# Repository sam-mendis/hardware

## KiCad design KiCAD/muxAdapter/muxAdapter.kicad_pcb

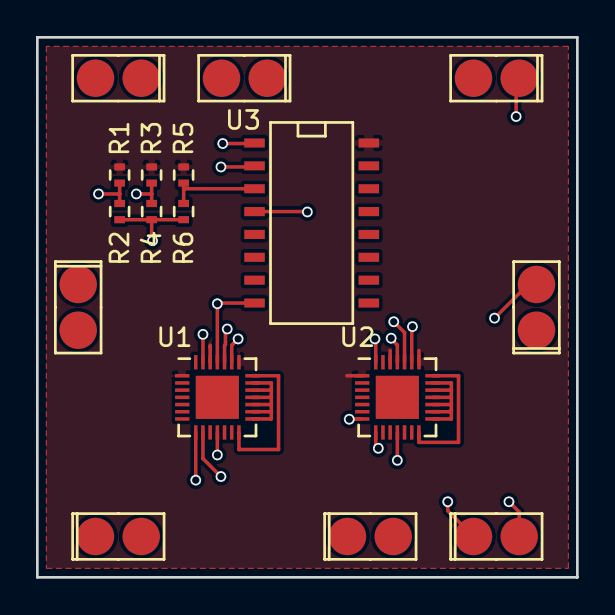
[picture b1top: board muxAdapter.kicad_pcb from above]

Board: 4 copper layers, 30.0 x 30.0 mm, 55 parts (38 on the bottom side), 29 nets.

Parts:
P1, P2, P3, P4, P5, P6, P7, P8, P9, P10, P11, P12, P13, P14, P15, P16, P17, P18, P19, P20, P21, P22, P23, P24, P25, P26, P27, P28, P29, P30, P31, P32, P33, P34, P35, P36, P37, P38: CONN_01X01; 0508-0-00-15-00-00-03-0
P39, P40, P41, P42, P43, P44, P45, P46: CONN_01X02; 812-22-002-30-007101
R1, R2, R3, R4, R5, R6: R; R_0402
U1, U2: MAX14662; QFN-28-1EP_4x4mm_Pitch0.4mm
U3: PCF8574; SO-16-N

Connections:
0_I: P40.2, U1.3
0_V: P40.1, U2.3
1_I: P41.1, U1.4
1_V: P41.2, U2.4
2_I: P42.2, U1.5
2_V: P42.1, U2.5
3_I: P43.1, U1.6
3_V: P43.2, U2.6
4_I: P44.2, U1.7
4_V: P44.1, U2.7
5_I: P45.1, U1.8
5_V: P45.2, U2.8
+5V: R1.1, R3.1, R5.1, U1.1, U1.22, U1.26, U2.1, U2.22, U2.26, U3.16
A0: R1.2, R2.1, U3.1
A1: R3.2, R4.1, U3.2
A2: R5.2, R6.1, U3.3
GND: R2.2, R4.2, R6.2, U1.11, U1.25, U2.11, U2.25, U3.8
I+: U1.15, U1.16, U1.17, U1.18, U1.19, U1.20
I-: U1.14, U1.21
L_I: P39.1, U1.2
L_V: P39.2, U2.2
MOSI: U1.27, U2.27
unnamed: U1.23, U2.28
R_I: P46.2, U1.9
R_V: P46.1, U2.9
SCK: U1.24, U2.24
SM_CS: U2.23, U3.4
V+: U2.15, U2.16, U2.17, U2.18, U2.19, U2.20
V-: U2.14, U2.21

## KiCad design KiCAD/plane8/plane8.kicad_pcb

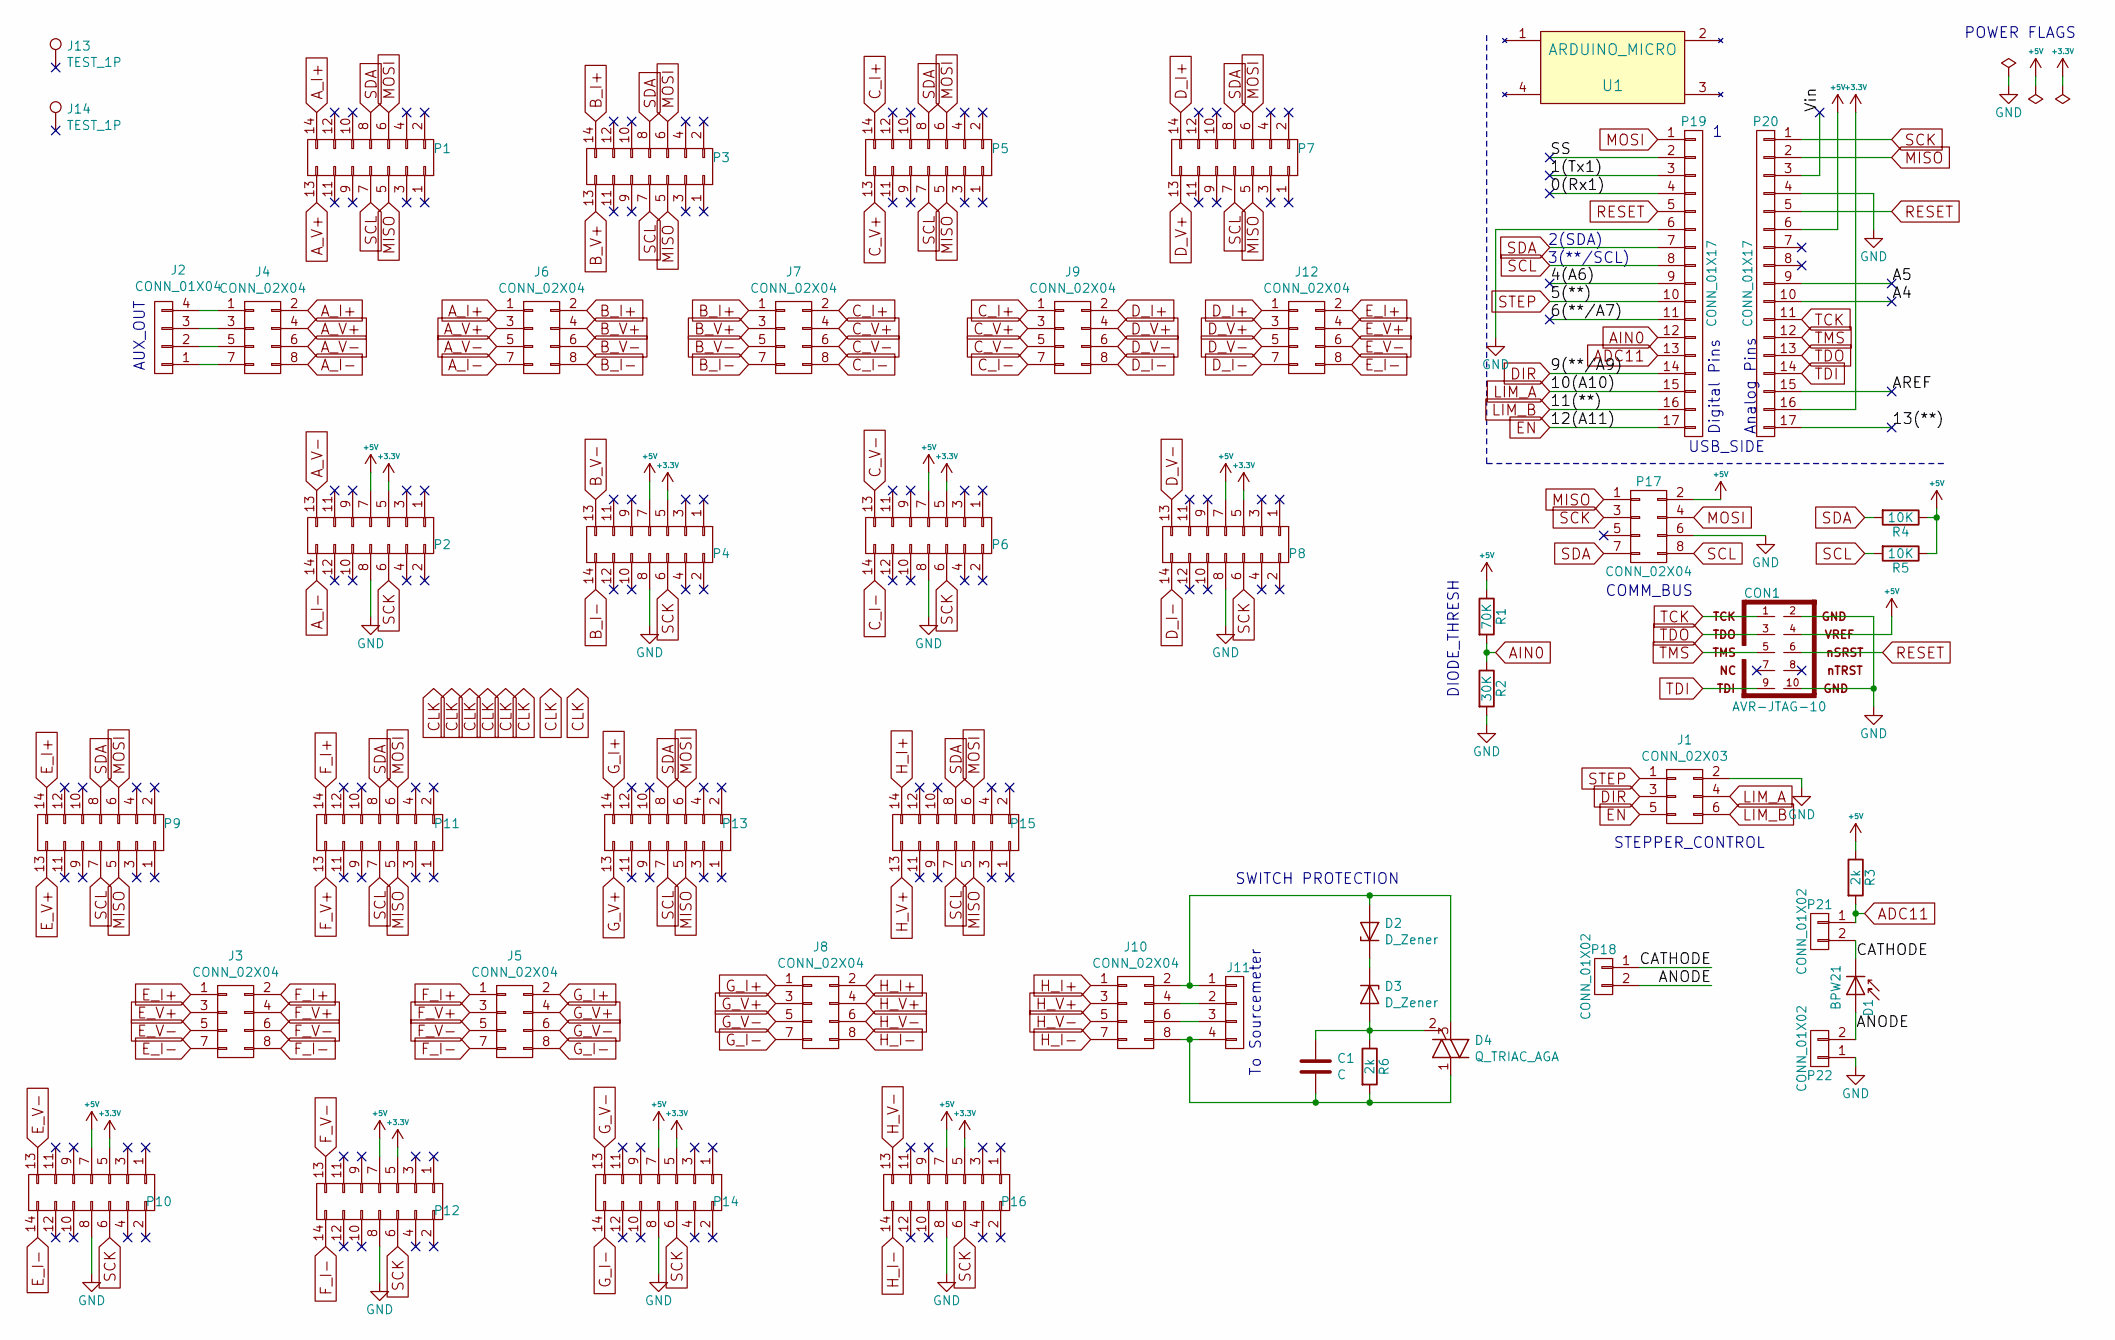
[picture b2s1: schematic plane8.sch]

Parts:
C1: C; C_0805_HandSoldering
CON1: AVR-JTAG-10; Pin_Header_Straight_2x05_Pitch2.54mm
D1: BPW21
D2, D3: D_Zener; D_DO-41_SOD81_P10.16mm_Horizontal
D4: Q_TRIAC_AGA; TO-92_Horizontal1_Molded_Narrow
J1: CONN_02X03; Pin_Header_Straight_2x03_Pitch2.54mm
J2, J11: CONN_01X04; Pin_Header_Angled_1x04_Pitch2.54mm
J3, J4, J5, J6, J7, J8, J9, J10, J12: CONN_02X04; Pin_Header_Straight_2x04_Pitch2.54mm
J13, J14: TEST_1P; MountingHole_2.2mm_M2_Pad
P1, P3, P5, P7, P9, P11, P13, P15: CONN_02X07; TSW-107-22-T-D-INV
P2, P4, P6, P8, P10, P12, P14, P16: CONN_02X07; TSW-107-22-T-D
P17: CONN_02X04; Pin_Header_Straight_2x04_Pitch2.54mm
P18, P21, P22: CONN_01X02; Pin_Header_Straight_1x02_Pitch2.54mm
P19, P20: CONN_01X17; Socket_Strip_Straight_1x17_Pitch2.54mm
R1: 70K; R_0805_HandSoldering
R2: 30K; R_0805_HandSoldering
R3, R6: 2k; R_0805_HandSoldering
R4, R5: 10K; R_0805_HandSoldering
U1: ARDUINO_MICRO; arduino_micro

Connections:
+3V3: P2.5, P4.5, P6.5, P8.5, P10.5, P12.5, P14.5, P16.5, P20.16
+5V: CON1.4, P2.7, P4.7, P6.7, P8.7, P10.7, P12.7, P14.7, P16.7, P17.2, P20.6, R1.1, R3.1, R4.1, R5.1
/0(Rx1): P19.4
/1(Tx1): P19.3
/4(A6): P19.9
/6(**/A7): P19.11
/13(**): P20.17
/A4: P20.10
/A5: P20.9
/ANODE: D1.2 (A), P18.2, P22.2
/AREF: P20.15
/CATHODE: D1.1 (K), P18.1, P21.2
/SS: P19.2
/Vin: P20.3
ADC11: P19.13, P21.1, R3.2
AIN0: P19.12, R1.2, R2.1
A_I+: J4.2, J6.1, P1.14
A_I-: J4.8, J6.7, P2.14
A_V+: J4.4, J6.3, P1.13
A_V-: J4.6, J6.5, P2.13
B_I+: J6.2, J7.1, P3.14
B_I-: J6.8, J7.7, P4.14
B_V+: J6.4, J7.3, P3.13
B_V-: J6.6, J7.5, P4.13
C_I+: J7.2, J9.1, P5.14
C_I-: J7.8, J9.7, P6.14
C_V+: J7.4, J9.3, P5.13
C_V-: J7.6, J9.5, P6.13
DIR: J1.3, P19.14
D_I+: J9.2, J12.1, P7.14
D_I-: J9.8, J12.7, P8.14
D_V+: J9.4, J12.3, P7.13
D_V-: J9.6, J12.5, P8.13
EN: J1.5, P19.17
E_I+: J3.1, J12.2, P9.14
E_I-: J3.7, J12.8, P10.14
E_V+: J3.3, J12.4, P9.13
E_V-: J3.5, J12.6, P10.13
F_I+: J3.2, J5.1, P11.14
F_I-: J3.8, J5.7, P12.14
F_V+: J3.4, J5.3, P11.13
F_V-: J3.6, J5.5, P12.13
GND: CON1.2, CON1.10, J1.2, P2.8, P4.8, P6.8, P8.8, P10.8, P12.8, P14.8, P16.8, P17.6, P19.6, P20.4, P22.1, R2.2
G_I+: J5.2, J8.1, P13.14
G_I-: J5.8, J8.7, P14.14
G_V+: J5.4, J8.3, P13.13
G_V-: J5.6, J8.5, P14.13
H_I+: J8.2, J10.1, P15.14
H_I-: J8.8, J10.7, P16.14
H_V+: J8.4, J10.3, P15.13
H_V-: J8.6, J10.5, P16.13
LIM_A: J1.4, P19.15
LIM_B: J1.6, P19.16
MISO: P1.5, P3.5, P5.5, P7.5, P9.5, P11.5, P13.5, P15.5, P17.1, P20.2
MOSI: P1.6, P3.6, P5.6, P7.6, P9.6, P11.6, P13.6, P15.6, P17.4, P19.1
unnamed: C1.1, D3.2 (A), D4.2 (G), R6.1
unnamed: C1.2, D4.1 (A1), J10.8, J11.4, R6.2
unnamed: D2.1 (K), D3.1 (K)
unnamed: D2.2 (A), D4.3 (A2), J10.2, J11.1
unnamed: J2.1, J4.7
unnamed: J2.2, J4.5
unnamed: J2.3, J4.3
unnamed: J2.4, J4.1
unnamed: J10.4, J11.2
unnamed: J10.6, J11.3
RESET: CON1.6, P19.5, P20.5
SCK: P2.6, P4.6, P6.6, P8.6, P10.6, P12.6, P14.6, P16.6, P17.3, P20.1
SCL: P1.7, P3.7, P5.7, P7.7, P9.7, P11.7, P13.7, P15.7, P17.8, P19.8, R5.2
SDA: P1.8, P3.8, P5.8, P7.8, P9.8, P11.8, P13.8, P15.8, P17.7, P19.7, R4.2
STEP: J1.1, P19.10
TCK: CON1.1, P20.11
TDI: CON1.9, P20.14
TDO: CON1.3, P20.13
TMS: CON1.5, P20.12

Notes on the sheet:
3(**/SCL)
2(SDA)
Digital Pins
Analog Pins
COMM_BUS
USB_SIDE
POWER FLAGS
STEPPER_CONTROL
To Sourcemeter
AUX_OUT
DIODE_THRESH
SWITCH PROTECTION

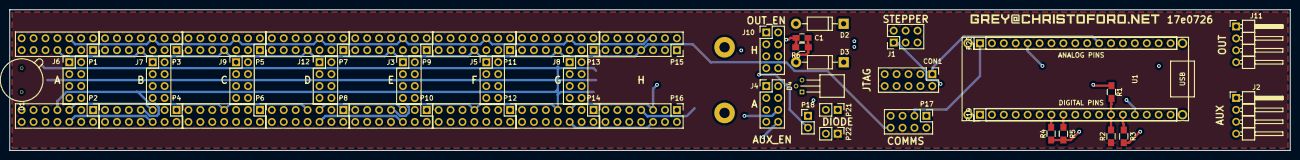
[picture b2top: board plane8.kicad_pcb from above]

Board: 4 copper layers, 273.0 x 30.0 mm, 49 parts (0 on the bottom side), 64 nets.

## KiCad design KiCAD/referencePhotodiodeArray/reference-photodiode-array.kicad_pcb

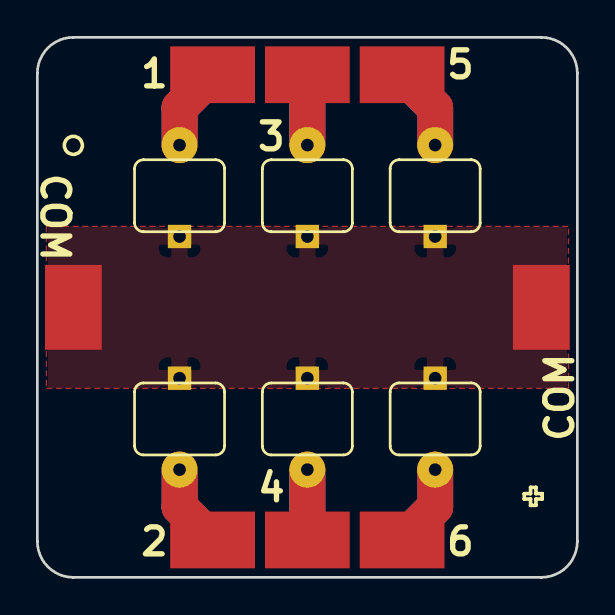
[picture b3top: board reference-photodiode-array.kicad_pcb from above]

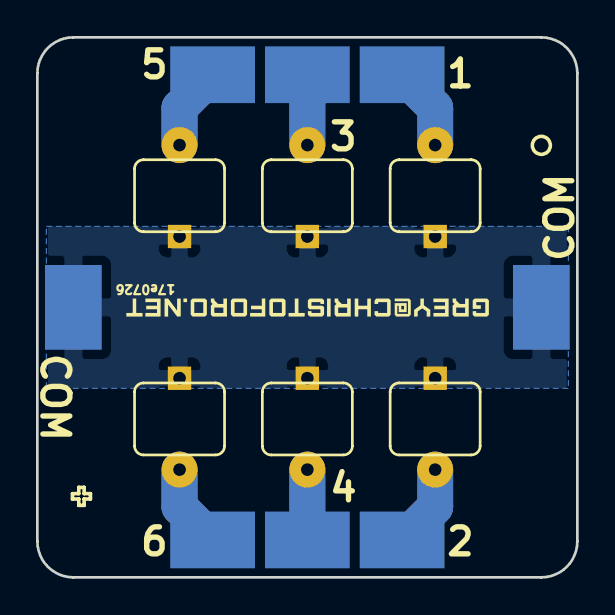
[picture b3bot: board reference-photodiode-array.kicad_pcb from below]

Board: 2 copper layers, 30.0 x 30.0 mm, 22 parts (14 on the bottom side), 7 nets.

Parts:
D1, D2, D3, D4, D5, D6: D_Photo; BPW34
W1, W2, W3, W4, W5, W6, W7, W10, W11, W12, W13, W14, W15, W16, W17, W20: TEST_1P; SolderWirePad_single_SMD_4.7x3.2mm

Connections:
/com: D1.1, D2.1, D3.1, D4.1, D5.1, D6.1, W1.1, W10.1, W11.1, W20.1
unnamed: D1.2, W2.1, W12.1
unnamed: D2.2, W3.1, W13.1
unnamed: D3.2, W4.1, W14.1
unnamed: D4.2, W5.1, W15.1
unnamed: D5.2, W6.1, W16.1
unnamed: D6.2, W7.1, W17.1

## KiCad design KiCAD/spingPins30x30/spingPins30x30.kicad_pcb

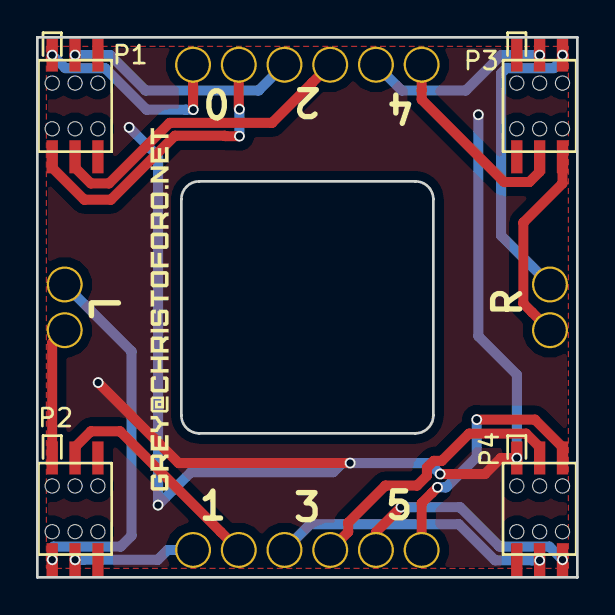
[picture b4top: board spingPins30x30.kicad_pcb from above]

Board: 2 copper layers, 30.0 x 30.0 mm, 20 parts (0 on the bottom side), 16 nets.

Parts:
P1, P2, P3, P4: CONN_02X03; RSM-103-02-L-D
TP1, TP2, TP3, TP4, TP5, TP6, TP7, TP8, TP9, TP10, TP11, TP12, TP13, TP14, TP15, TP16: TEST; S25-022+P25-4023

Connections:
0_I: P1.2, TP5.1
0_V: P1.1, TP3.1
1_I: P2.4, TP4.1
1_V: P2.3, TP6.1
2_I: P1.4, TP9.1
2_V: P1.3, TP7.1
3_I: P4.4, TP8.1
3_V: P4.3, TP10.1
4_I: P3.4, TP13.1
4_V: P3.3, TP11.1
5_I: P4.6, TP12.1
5_V: P4.5, TP14.1
L_I: P2.2, TP2.1
L_V: P2.1, TP1.1
R_I: P3.6, TP16.1
R_V: P3.5, TP15.1

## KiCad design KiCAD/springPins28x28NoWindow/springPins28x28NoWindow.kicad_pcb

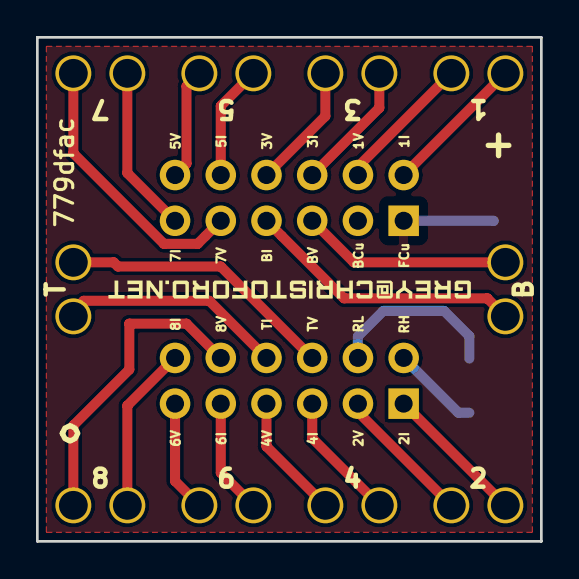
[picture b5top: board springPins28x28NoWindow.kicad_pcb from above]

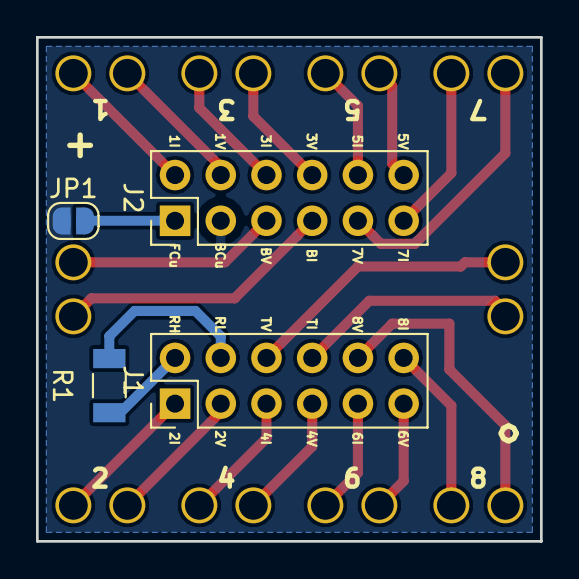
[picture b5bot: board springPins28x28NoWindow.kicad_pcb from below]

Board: 2 copper layers, 28.0 x 28.0 mm, 25 parts (4 on the bottom side), 24 nets.

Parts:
J1, J2: CONN_02X06; PinHeader_2x06_P2.54mm_Vertical
JP1: Jumper_NC_Small; SolderJumper-2_P1.3mm_Open_RoundedPad1.0x1.5mm
L1: GREY@CHRISTOFORO.NET; logo_small
R1: 100k; R_1206_3216Metric
TP1, TP2, TP3, TP4, TP5, TP6, TP7, TP8, TP9, TP10, TP11, TP12, TP13, TP14, TP15, TP16, TP17, TP18, TP19, TP20: TEST; S25-022+P25-4023

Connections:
/BCu: J2.3, JP1.1
/FCu: J2.1, JP1.2
/I1: J2.2, TP20.1
/I2: J1.1, TP8.1
/I3: J2.6, TP18.1
/I4: J1.5, TP6.1
/I5: J2.10, TP16.1
/I6: J1.9, TP4.1
/I7: J2.11, TP14.1
/I8: J1.12, TP2.1
/IB: J2.7, TP10.1
/IT: J1.8, TP9.1
/RH: J1.2, R1.2
/RL: J1.4, R1.1
/V1: J2.4, TP19.1
/V2: J1.3, TP7.1
/V3: J2.8, TP17.1
/V4: J1.7, TP5.1
/V5: J2.12, TP15.1
/V6: J1.11, TP3.1
/V7: J2.9, TP13.1
/V8: J1.10, TP1.1
/VB: J2.5, TP12.1
/VT: J1.6, TP11.1

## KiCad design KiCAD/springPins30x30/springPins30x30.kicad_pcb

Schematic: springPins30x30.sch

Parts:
J1, J2, J3, J4, J5, J6, J7, J8: CONN_01X03; M50-3130342
TP1, TP2, TP3, TP4, TP5, TP6, TP7, TP8, TP9, TP10, TP11, TP12, TP13, TP14, TP15, TP16: TEST; S25-022+P25-4023

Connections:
0_I: J2.1, TP5.1
0_V: J1.1, TP3.1
1_I: J3.2, TP4.1
1_V: J4.2, TP6.1
2_I: J2.2, TP9.1
2_V: J1.2, TP7.1
3_I: J7.2, TP8.1
3_V: J8.2, TP10.1
4_I: J6.2, TP13.1
4_V: J5.2, TP11.1
5_I: J7.1, TP12.1
5_V: J8.1, TP14.1
+3V3: J3.1
+5V: J7.3
/MISO: J1.3
/MOSI: J2.3
/SCK: J4.1
/SCL: J5.1
/SDA: J6.1
GND: J8.3
L_I: J3.3, TP2.1
L_V: J4.3, TP1.1
R_I: J6.3, TP16.1
R_V: J5.3, TP15.1

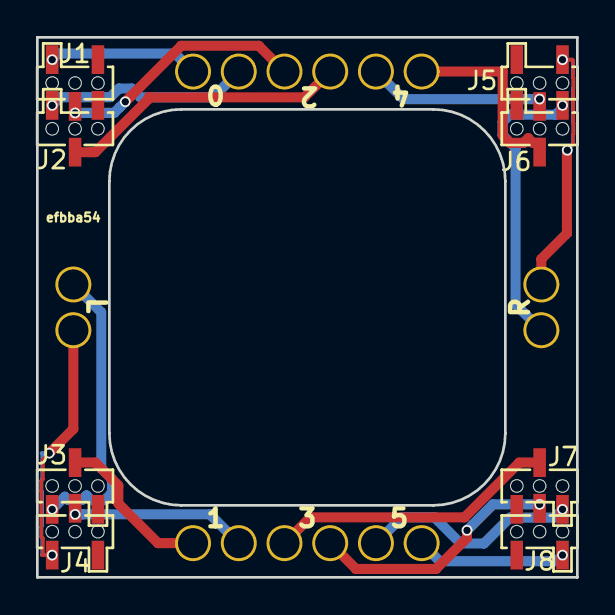
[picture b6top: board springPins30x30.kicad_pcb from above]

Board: 2 copper layers, 30.0 x 30.0 mm, 24 parts (0 on the bottom side), 16 nets.
